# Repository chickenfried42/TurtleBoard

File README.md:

# TurtleBoard
The TurtleBoard is a development board based on the RP2040 chip. It features 43 pins, including most standard GPIO pins, an onboard potentiometer, and LED.<br>
I made this board to learn PCB design and to understand the inner workings of dev boards. This was hell to figure out for the first time, but insanely rewarding and probably more educational than anything I ever did at school. 
Front:

Back:

Sadly, the back has no silly drawing, which is because my KiCad kept crashing whenever I tried doing anything with it, so I left it alone out of fear of corrupting the design file or something.

# Schematic

# PCB

# JLCPCB Render

# BOM
|Reference                      |Quantity|Comment                    |Total Cost|Part #|Exclude from Board|Footprint                                                 |Datasheet                                                                        |
|-------------------------------|--------|---------------------------|---|----------------|------------------|----------------------------------------------------------|---------------------------------------------------------------------------------|
|C1,C10                         |2       |1uF                        |$0.04|CL05A105KA5NQNC|                  |Capacitor_SMD:C_0402_1005Metric                           |~                                                                                |
|C2,C3,C4,C5,C6,C7,C8,C9,C11,C12,C17|10      |0.1uF                      |$0.0825|CL05B104KO5NNNC|                  |Capacitor_SMD:C_0402_1005Metric                           |~                                                                                |
|C13,C14                        |2       |10uF                       |$0.102|CL10A106KP8NNNC|                  |Capacitor_SMD:C_0603_1608Metric                           |~                                                                                |
|C15,C16                        |2       |33pF                       |$0.013|0402CG330J500NT|                  |Capacitor_SMD:C_0402_1005Metric                           |~                                                                                |
|D1                             |1       |LED                        |$0.332|16-213SDRC/S530-A3/TR8|                  |LED_SMD:LED_0402_1005Metric                               |~                                                                                |
|J1                             |1       |USB_C_Receptacle_USB2.0_14P|$0.918|TYPE-C-31-M-12|                  |Connector_USB:USB_C_Receptacle_HRO_TYPE-C-31-M-12         |https://www.usb.org/sites/default/files/documents/usb_type-c.zip                 |
|J2,J3                          |2       |Conn_01x20                 |$1.36   |2.54-1*20P直针|                  |Connector_PinHeader_2.54mm:PinHeader_1x20_P2.54mm_Vertical|~                                                                                |
|J4                             |1       |Conn_01x03                 |$0.2488|1.27-1*3P针|                  |Connector_PinHeader_2.54mm:PinHeader_1x03_P2.54mm_Vertical|~                                                                                |
|R1,R2                          |2       |5.1K                       |$0.009|0402WGF5101TCE|                  |Resistor_SMD:R_0402_1005Metric                            |~                                                                                |
|R3,R4                          |2       |27                         |$0.0176|0402WGF270JTCE|                  |Resistor_SMD:R_0402_1005Metric                            |~                                                                                |
|R5,R7                          |2       |1K                         |$0.01|0402WGF1001TCE|                  |Resistor_SMD:R_0402_1005Metric                            |~                                                                                |
|R6                             |1       |10K                        |$0.0065|0402WGF1002TCE|                  |Resistor_SMD:R_0402_1005Metric                            |~                                                                                |
|R9                             |1       |220                        |$0.0045|0402WGF2200TCE|                  |Resistor_SMD:R_0402_1005Metric                            |~                                                                                |
|RV1                            |1       |R_Potentiometer            |$13.544   |3214J-1-503E|                  |Potentiometer_SMD:Potentiometer_Bourns_3214J_Horizontal   |~                                                                                |
|SW1                            |1       |SW_Push                    |$0.028|TS-1088-AR02016|                  |Button_Switch_SMD:SW_Push_SPST_NO_Alps_SKRK               |~                                                                                |
|U1                             |1       |RP2040                     |$4.8940|RP2040|                  |Package_DFN_QFN:QFN-56-1EP_7x7mm_P0.4mm_EP3.2x3.2mm       |https://datasheets.raspberrypi.com/rp2040/rp2040-datasheet.pdf                   |
|U2                             |1       |MCP1700x-330xxTT           |$2.398|MCP1700T-3302E/TT|                  |Package_TO_SOT_SMD:SOT-23                                 |http://ww1.microchip.com/downloads/en/DeviceDoc/20001826D.pdf                    |
|U3                             |1       |W25Q16JVZPIQ TR            |$8.0815|W25Q16JVUXIQ|                  |Package_SON:Winbond_USON-8-1EP_3x2mm_P0.5mm_EP0.2x1.6mm   |https://www.winbond.com/resource-files/w25q128jv_dtr%20revc%2003272018%20plus.pdf|
|Y1                             |1       |12MHz                      |$0.368|X322512MSB4SI|                  |Crystal:Crystal_SMD_3225-4Pin_3.2x2.5mm                   |~                                                                                |

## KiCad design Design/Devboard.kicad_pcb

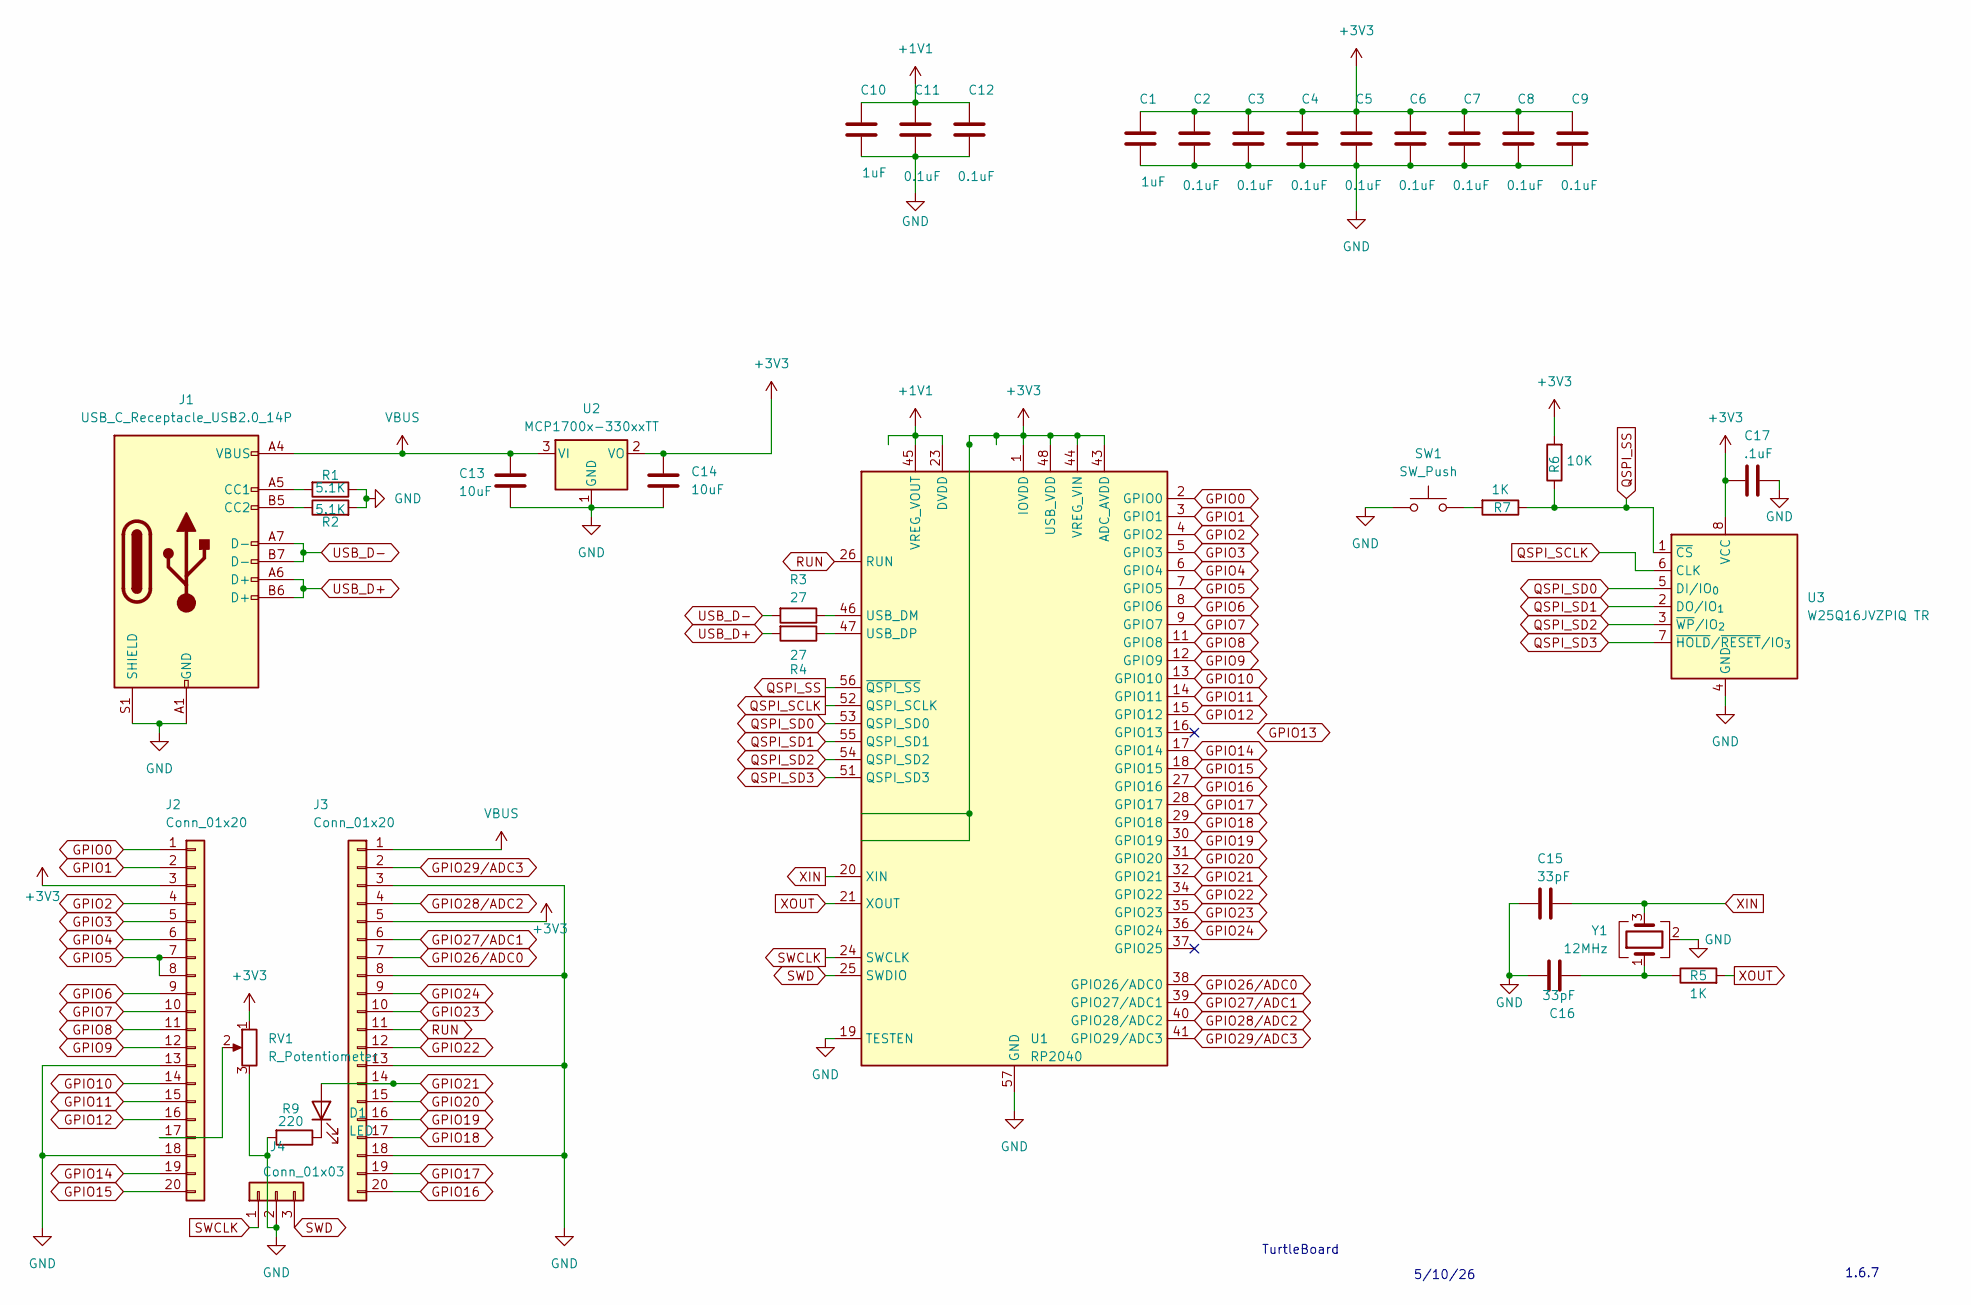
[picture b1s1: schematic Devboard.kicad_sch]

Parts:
C1, C10: 1uF; C_0402_1005Metric
C2, C3, C4, C5, C6, C7, C8, C9, C11, C12: 0.1uF; C_0402_1005Metric
C13, C14: 10uF; C_0603_1608Metric
C15, C16: 33pF; C_0402_1005Metric
C17: .1uF; C_0402_1005Metric
D1: LED; LED_0402_1005Metric
J1: USB_C_Receptacle_USB2.0_14P; USB_C_Receptacle_HRO_TYPE-C-31-M-12
J2, J3: Conn_01x20; PinHeader_1x20_P2.54mm_Vertical
J4: Conn_01x03; PinHeader_1x03_P2.54mm_Vertical
R1, R2: 5.1K; R_0402_1005Metric
R3, R4: 27; R_0402_1005Metric
R5, R7: 1K; R_0402_1005Metric
R6: 10K; R_0402_1005Metric
R9: 220; R_0402_1005Metric
RV1: R_Potentiometer; Potentiometer_Bourns_3214J_Horizontal
SW1: SW_Push; SW_Push_SPST_NO_Alps_SKRK
U1: RP2040; QFN-56-1EP_7x7mm_P0.4mm_EP3.2x3.2mm
U2: MCP1700x-330xxTT; SOT-23
U3: W25Q16JVZPIQ TR; Winbond_USON-8-1EP_3x2mm_P0.5mm_EP0.2x1.6mm
Y1: 12MHz; Crystal_SMD_3225-4Pin_3.2x2.5mm

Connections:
+1V1: C10.1, C11.1, C12.1, U1.23 (DVDD), U1.45 (VREG_VOUT), U1.50 (DVDD)
+3V3: C1.1, C2.1, C3.1, C4.1, C5.1, C6.1, C7.1, C8.1, C9.1, C14.1, C17.1, J2.3, J3.5, R6.2, RV1.1, U1.1 (IOVDD), U1.10 (IOVDD), U1.22 (IOVDD), U1.33 (IOVDD), U1.42 (IOVDD), U1.43 (ADC_AVDD), U1.44 (VREG_VIN), U1.48 (USB_VDD), U1.49 (IOVDD), U2.2 (VO), U3.8 (VCC)
GND: C1.2, C2.2, C3.2, C4.2, C5.2, C6.2, C7.2, C8.2, C9.2, C10.2, C11.2, C12.2, C13.2, C14.2, C15.1, C16.2, C17.2, J1.A1 (GND), J1.A12 (GND), J1.B1 (GND), J1.B12 (GND), J1.S1 (SHIELD), J2.13, J2.18, J3.3, J3.8, J3.13, J3.18, J4.2, R1.1, R2.2, R9.2, RV1.3, SW1.1, U1.19 (TESTEN), U1.57 (GND), U2.1 (GND), U3.4 (GND), Y1.2 (G), Y1.4 (G)
GPIO0: J2.1, U1.2 (GPIO0)
GPIO1: J2.2, U1.3 (GPIO1)
GPIO2: J2.4, U1.4 (GPIO2)
GPIO3: J2.5, U1.5 (GPIO3)
GPIO4: J2.6, U1.6 (GPIO4)
GPIO5: J2.7, J2.8, U1.7 (GPIO5)
GPIO6: J2.9, U1.8 (GPIO6)
GPIO7: J2.10, U1.9 (GPIO7)
GPIO8: J2.11, U1.11 (GPIO8)
GPIO9: J2.12, U1.12 (GPIO9)
GPIO10: J2.14, U1.13 (GPIO10)
GPIO11: J2.15, U1.14 (GPIO11)
GPIO12: J2.16, U1.15 (GPIO12)
GPIO14: J2.19, U1.17 (GPIO14)
GPIO15: J2.20, U1.18 (GPIO15)
GPIO16: J3.20, U1.27 (GPIO16)
GPIO17: J3.19, U1.28 (GPIO17)
GPIO18: J3.17, U1.29 (GPIO18)
GPIO19: J3.16, U1.30 (GPIO19)
GPIO20: J3.15, U1.31 (GPIO20)
GPIO21: D1.2 (A), J3.14, U1.32 (GPIO21)
GPIO22: J3.12, U1.34 (GPIO22)
GPIO23: J3.10, U1.35 (GPIO23)
GPIO24: J3.9, U1.36 (GPIO24)
GPIO26/ADC0: J3.7, U1.38 (GPIO26/ADC0)
GPIO27/ADC1: J3.6, U1.39 (GPIO27/ADC1)
GPIO28/ADC2: J3.4, U1.40 (GPIO28/ADC2)
GPIO29/ADC3: J3.2, U1.41 (GPIO29/ADC3)
unnamed: C16.1, R5.1, Y1.1
unnamed: D1.1 (K), R9.1
unnamed: J1.A5 (CC1), R1.2
unnamed: J1.B5 (CC2), R2.1
unnamed: J2.17, RV1.2
unnamed: R7.2, SW1.2
unnamed: R3.1, U1.46 (USB_DM)
unnamed: R4.1, U1.47 (USB_DP)
QSPI_SCLK: U1.52 (QSPI_SCLK), U3.6 (CLK)
QSPI_SD0: U1.53 (QSPI_SD0), U3.5 (DI/IO_{0})
QSPI_SD1: U1.55 (QSPI_SD1), U3.2 (DO/IO_{1})
QSPI_SD2: U1.54 (QSPI_SD2), U3.3 (~WP/IO_{2})
QSPI_SD3: U1.51 (QSPI_SD3), U3.7 (~HOLD/~RESET/IO_{3})
QSPI_SS: R6.1, R7.1, U1.56 (~QSPI_SS), U3.1 (~CS)
RUN: J3.11, U1.26 (RUN)
SWCLK: J4.1, U1.24 (SWCLK)
SWD: J4.3, U1.25 (SWDIO)
USB_D+: J1.A6 (D+), J1.B6 (D+), R4.2
USB_D-: J1.A7 (D-), J1.B7 (D-), R3.2
VBUS: C13.1, J1.A4 (VBUS), J1.A9 (VBUS), J1.B4 (VBUS), J1.B9 (VBUS), J3.1, U2.3 (VI)
XIN: C15.2, U1.20 (XIN), Y1.3
XOUT: R5.2, U1.21 (XOUT)

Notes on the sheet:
5/10/26
TurtleBoard
1.6.7

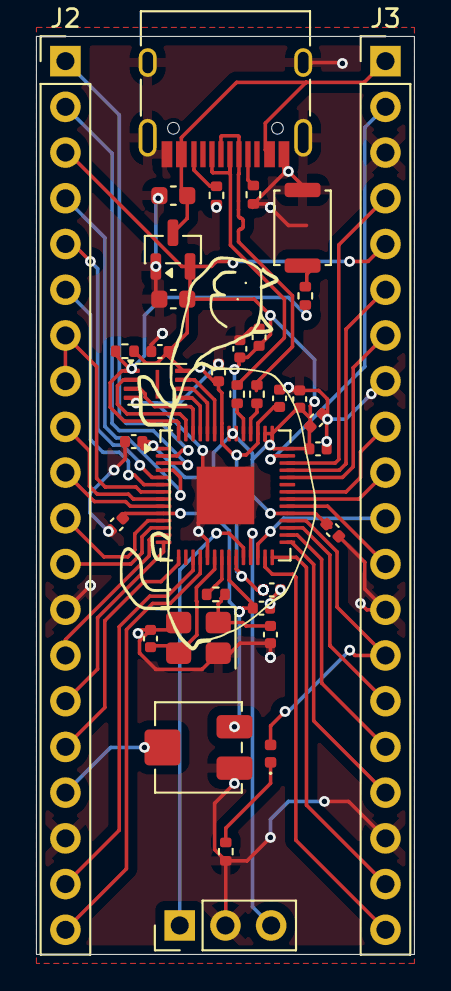
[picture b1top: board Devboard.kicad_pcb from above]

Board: 2 copper layers, 21.0 x 51.0 mm, 36 parts (0 on the bottom side), 53 nets.

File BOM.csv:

Comment,Designator,Footprint,Datasheet,Quantity
1uF,"C1,C10",Capacitor_SMD:C_0402_1005Metric,~,2
0.1uF,"C2,C3,C4,C5,C6,C7,C8,C9,C11,C12",Capacitor_SMD:C_0402_1005Metric,~,10
10uF,"C13,C14",Capacitor_SMD:C_0603_1608Metric,~,2
33pF,"C15,C16",Capacitor_SMD:C_0402_1005Metric,~,2
0.1uF,C17,Capacitor_SMD:C_0402_1005Metric,~,1
LED,D1,LED_SMD:LED_0402_1005Metric,~,1
USB_C_Receptacle_USB2.0_14P,J1,Connector_USB:USB_C_Receptacle_HRO_TYPE-C-31-M-12,https://www.usb.org/sites/default/files/documents/usb_type-c.zip,1
Conn_01x20,"J2,J3",Connector_PinHeader_2.54mm:PinHeader_1x20_P2.54mm_Vertical,~,2
Conn_01x03,J4,Connector_PinHeader_2.54mm:PinHeader_1x03_P2.54mm_Vertical,~,1
5.1K,"R1,R2",Resistor_SMD:R_0402_1005Metric,~,2
27,"R3,R4",Resistor_SMD:R_0402_1005Metric,~,2
1K,"R5,R7",Resistor_SMD:R_0402_1005Metric,~,2
10K,R6,Resistor_SMD:R_0402_1005Metric,~,1
220,R9,Resistor_SMD:R_0402_1005Metric,~,1
R_Potentiometer,RV1,Potentiometer_SMD:Potentiometer_Bourns_3214J_Horizontal,~,1
SW_Push,SW1,Button_Switch_SMD:SW_Push_SPST_NO_Alps_SKRK,~,1
RP2040,U1,Package_DFN_QFN:QFN-56-1EP_7x7mm_P0.4mm_EP3.2x3.2mm,https://datasheets.raspberrypi.com/rp2040/rp2040-datasheet.pdf,1
MCP1700x-330xxTT,U2,Package_TO_SOT_SMD:SOT-23,http://ww1.microchip.com/downloads/en/DeviceDoc/20001826D.pdf,1
W25Q16JVZPIQ TR,U3,Package_SON:Winbond_USON-8-1EP_3x2mm_P0.5mm_EP0.2x1.6mm,https://www.winbond.com/resource-files/w25q128jv_dtr%20revc%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,1
12MHz,Y1,Crystal:Crystal_SMD_3225-4Pin_3.2x2.5mm,~,1

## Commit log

2026-05-11 added files
    stuff
2026-05-11 deleted a file
    yea
2026-05-16 fixed bom
    ya
